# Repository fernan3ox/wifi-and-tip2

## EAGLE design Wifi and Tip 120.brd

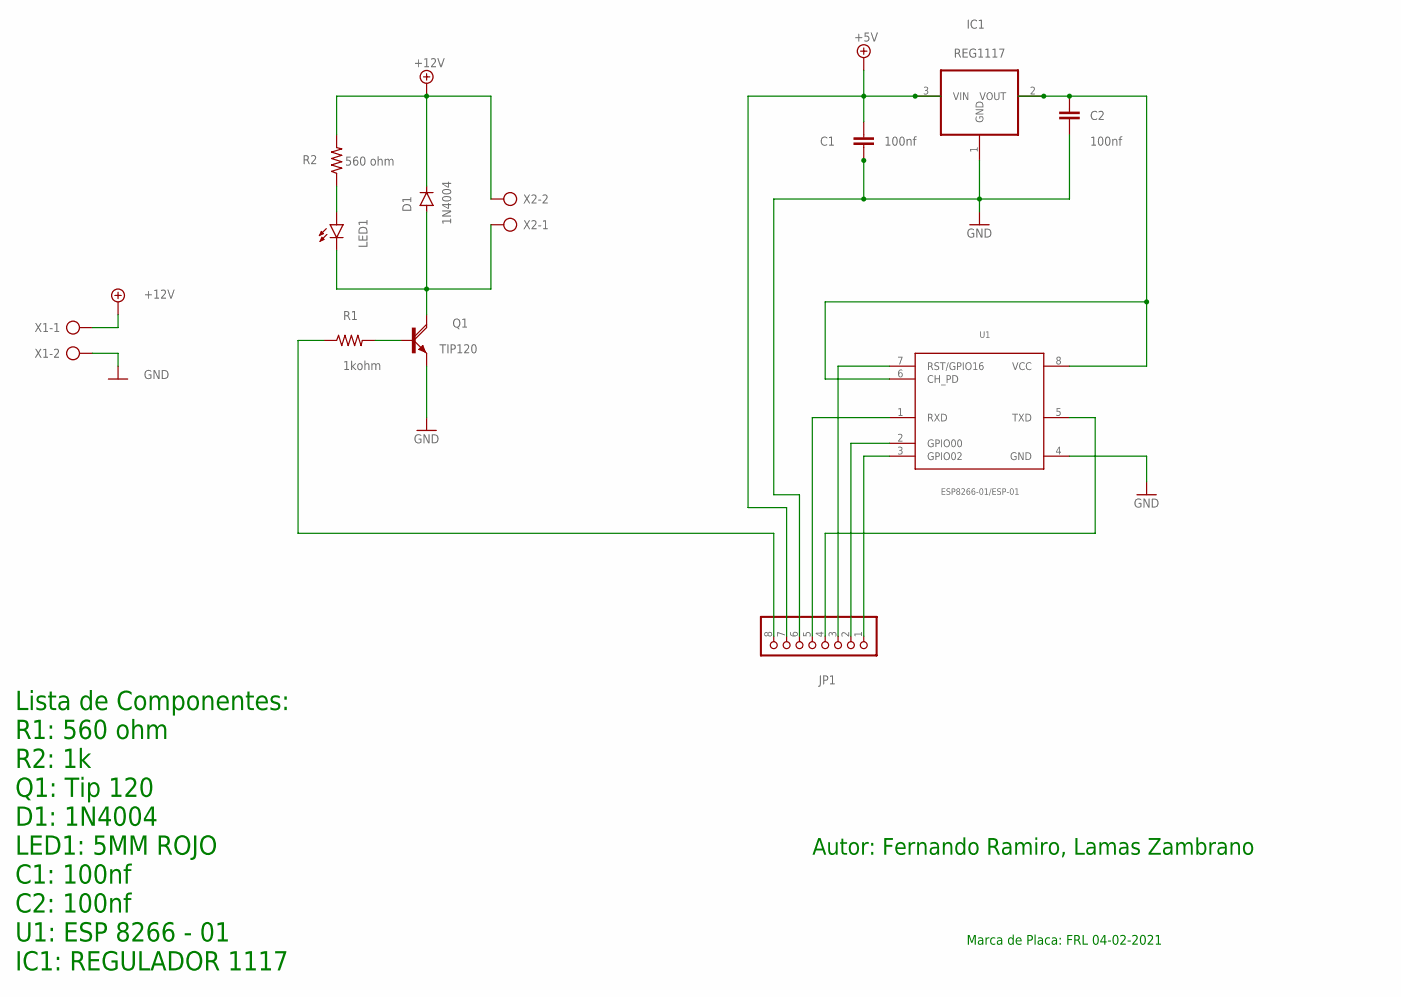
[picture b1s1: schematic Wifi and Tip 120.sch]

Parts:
C1, C2: 100nf; C025-024X044
D1: 1N4004; DO41-10
IC1: REG1117; SOT223
JP1: PINHD-1X8; 1X08
LED1: LED5MM
Q1: TIP120; TO220AH
R1: 1kohm; 0207/10
R2: 560 ohm; 0207/10
U1: ESP8266-01/ESP-01; XCVR_ESP8266-01/ESP-01
X1, X2: AK500/2

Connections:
+5V: C1.1, IC1.3 (VIN), JP1.7
+12V: D1.C, R2.2, X1.1, X2.2
GND: C1.2, C2.2, IC1.1 (GND), JP1.6, Q1.E, U1.4 (GND), X1.2
unnamed: Q1.B, R1.2
unnamed: D1.A, LED1.K (C), Q1.C, X2.1
unnamed: LED1.A, R2.1
unnamed: JP1.8, R1.1
unnamed: JP1.5, U1.1 (RXD)
unnamed: C2.1, IC1.2 (VOUT), U1.6 (CH_PD), U1.8 (VCC)
unnamed: JP1.4, U1.5 (TXD)
unnamed: JP1.3, U1.7 (RST/GPIO16)
unnamed: JP1.2, U1.2 (GPIO00)
unnamed: JP1.1, U1.3 (GPIO02)

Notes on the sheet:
Autor: Fernando Ramiro, Lamas Zambrano
Lista de Componentes: R1: 560 ohm R2: 1k Q1: Tip 120 D1: 1N4004 LED1: 5MM ROJO C1: 100nf C2: 100nf U1: ESP 8266 - 01 IC1: REGULADOR 1117
Marca de Placa: FRL 04-02-2021

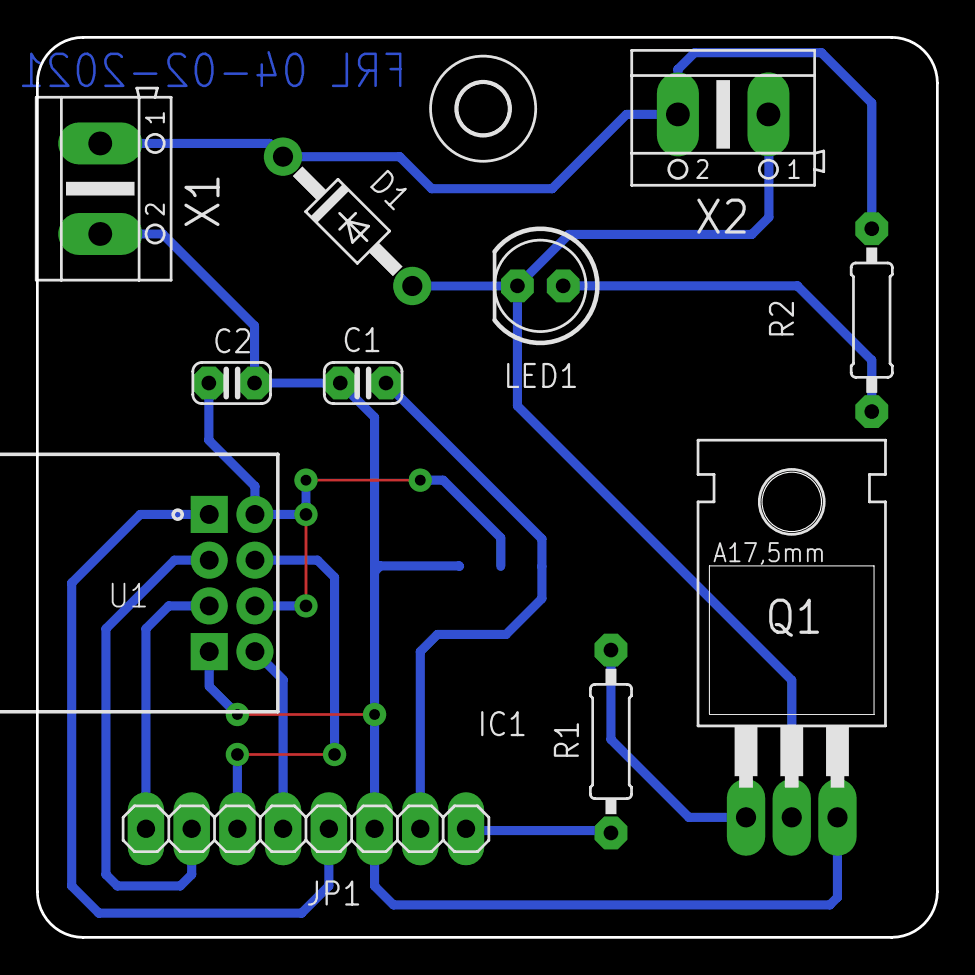
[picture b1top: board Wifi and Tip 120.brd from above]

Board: 2 copper layers, 50.0 x 50.0 mm, 13 parts (1 on the bottom side), 13 nets.

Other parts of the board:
U$1: 2,8

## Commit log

2021-09-06 ultima version
